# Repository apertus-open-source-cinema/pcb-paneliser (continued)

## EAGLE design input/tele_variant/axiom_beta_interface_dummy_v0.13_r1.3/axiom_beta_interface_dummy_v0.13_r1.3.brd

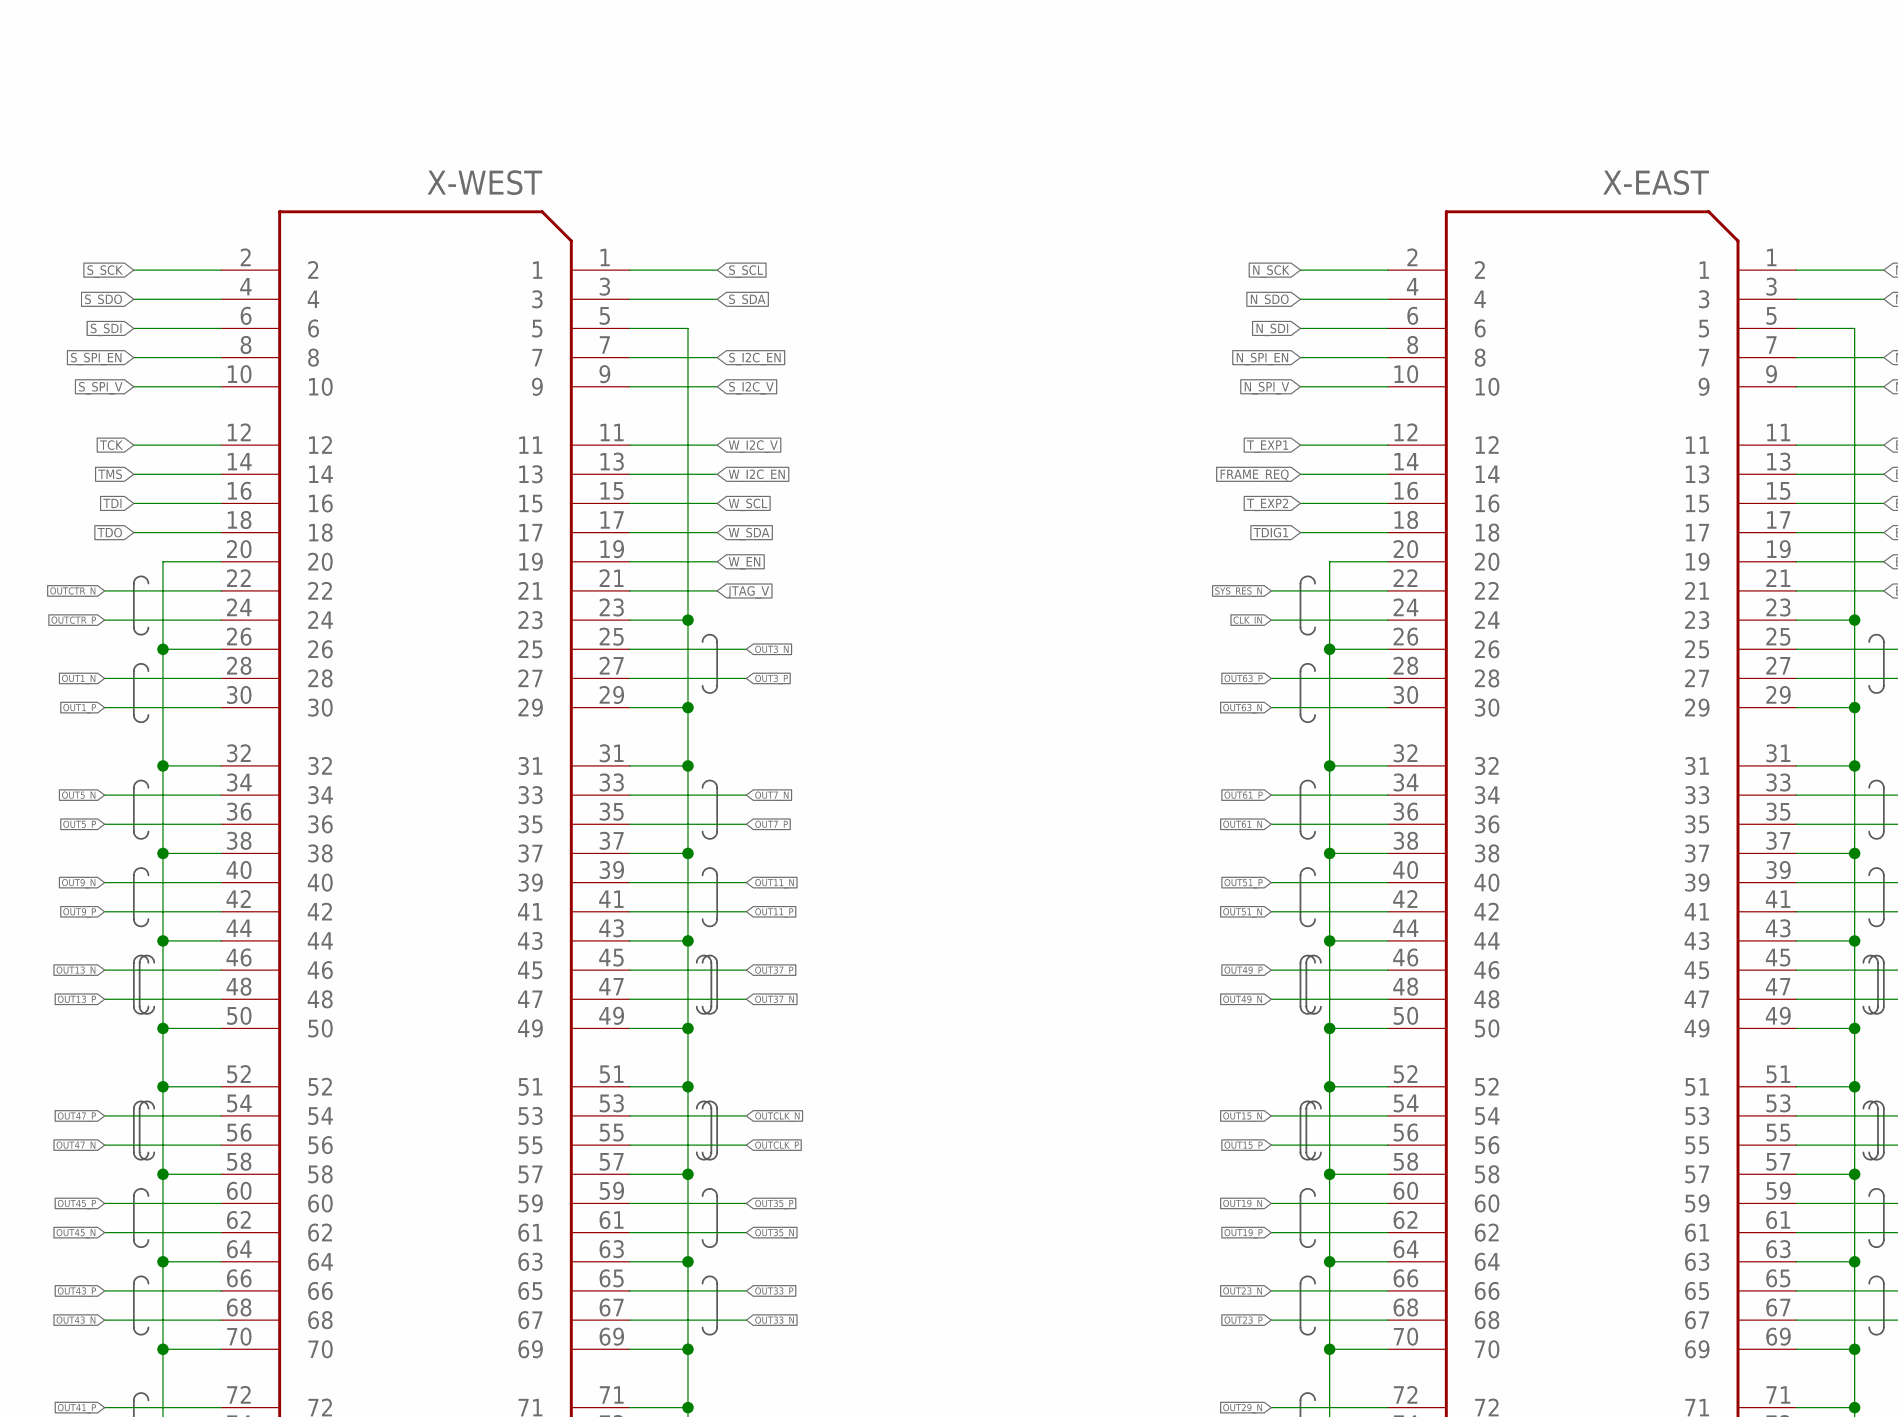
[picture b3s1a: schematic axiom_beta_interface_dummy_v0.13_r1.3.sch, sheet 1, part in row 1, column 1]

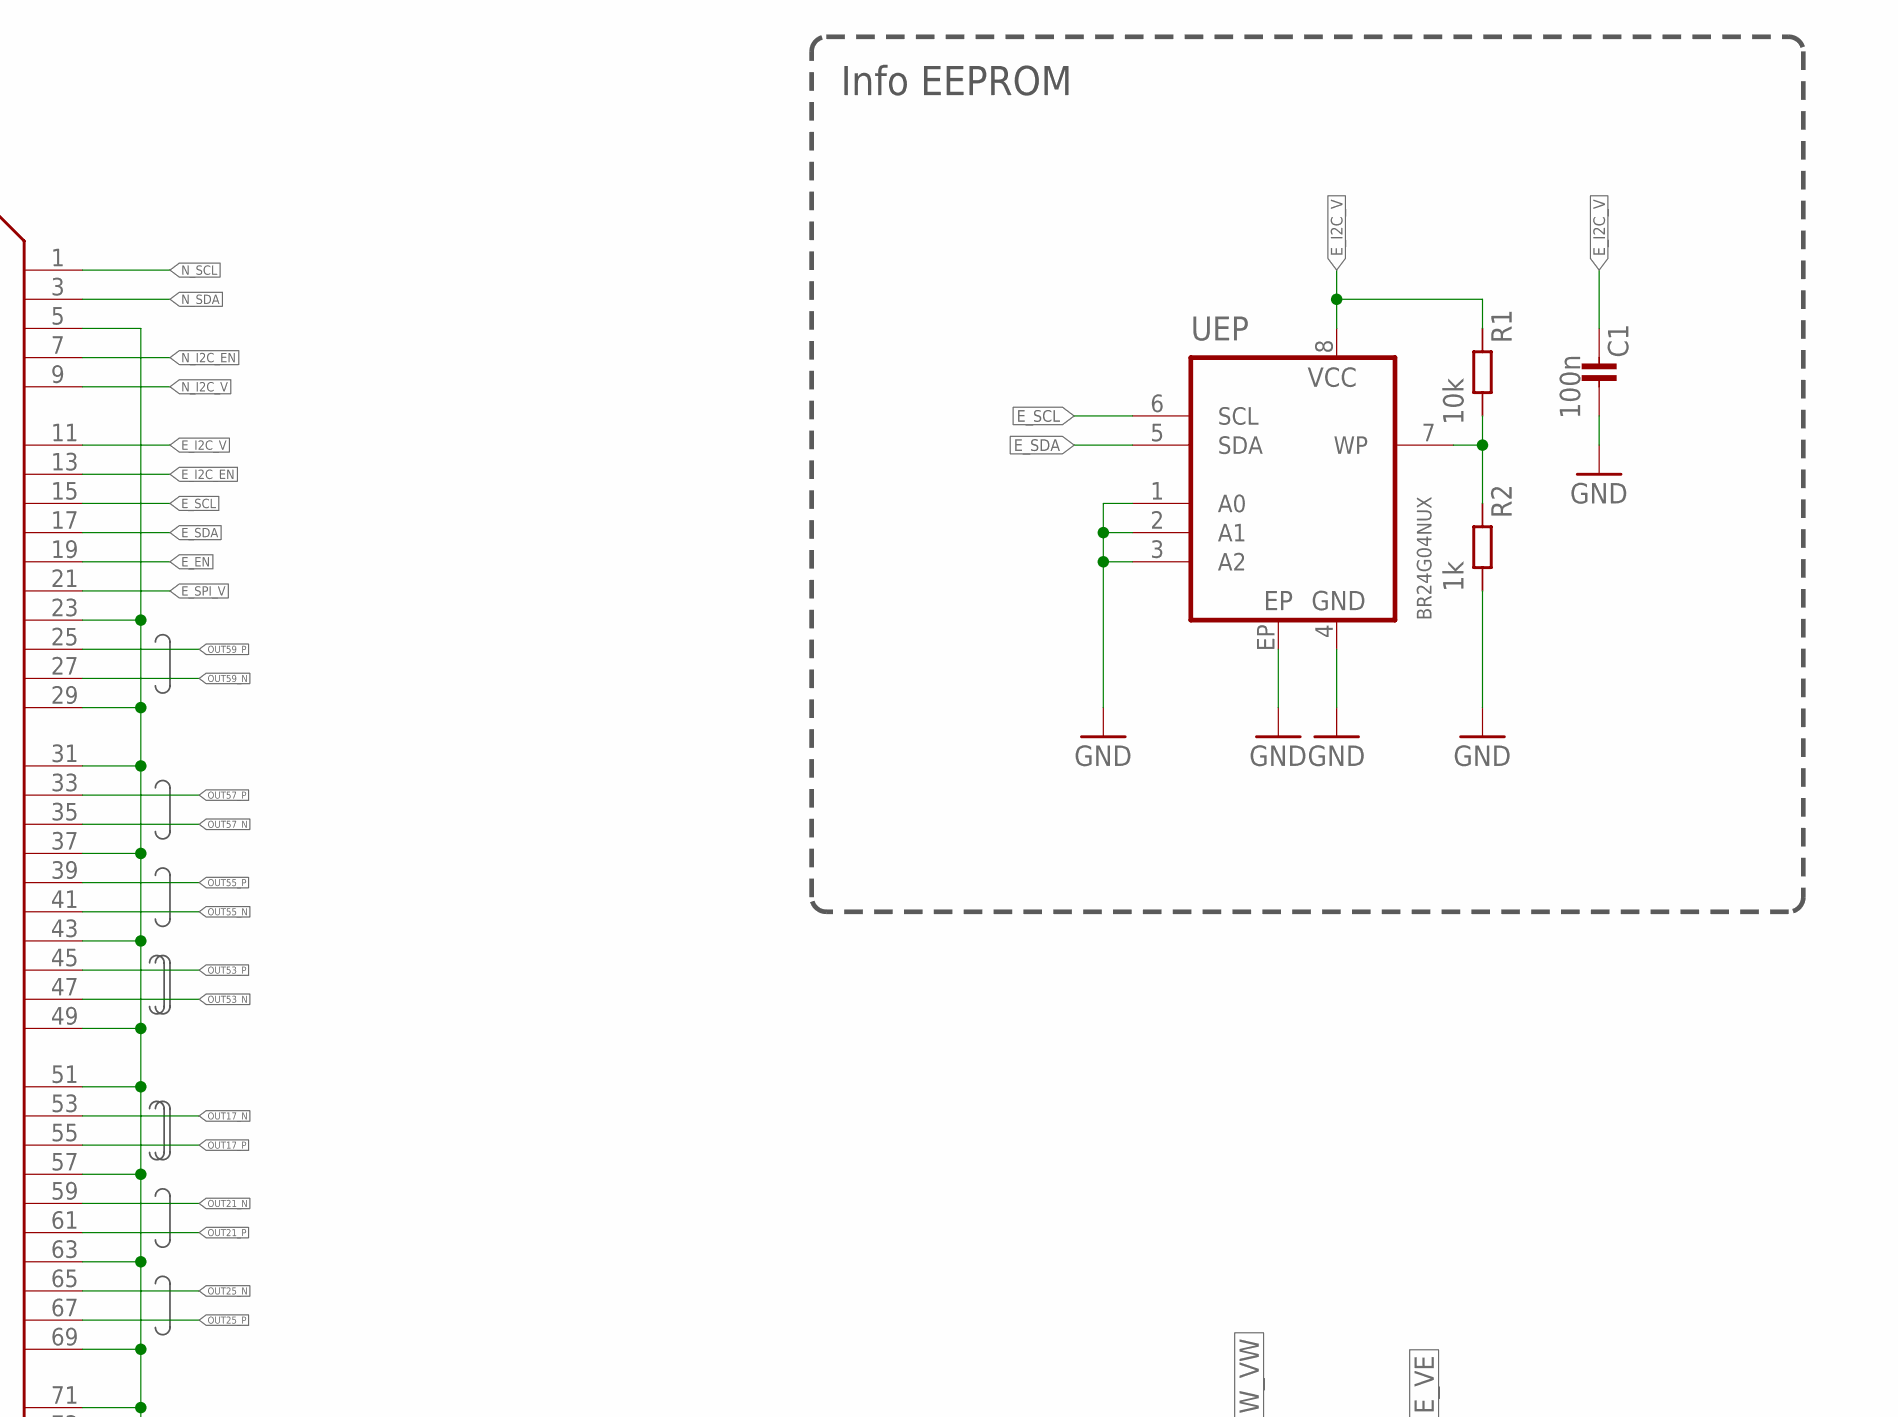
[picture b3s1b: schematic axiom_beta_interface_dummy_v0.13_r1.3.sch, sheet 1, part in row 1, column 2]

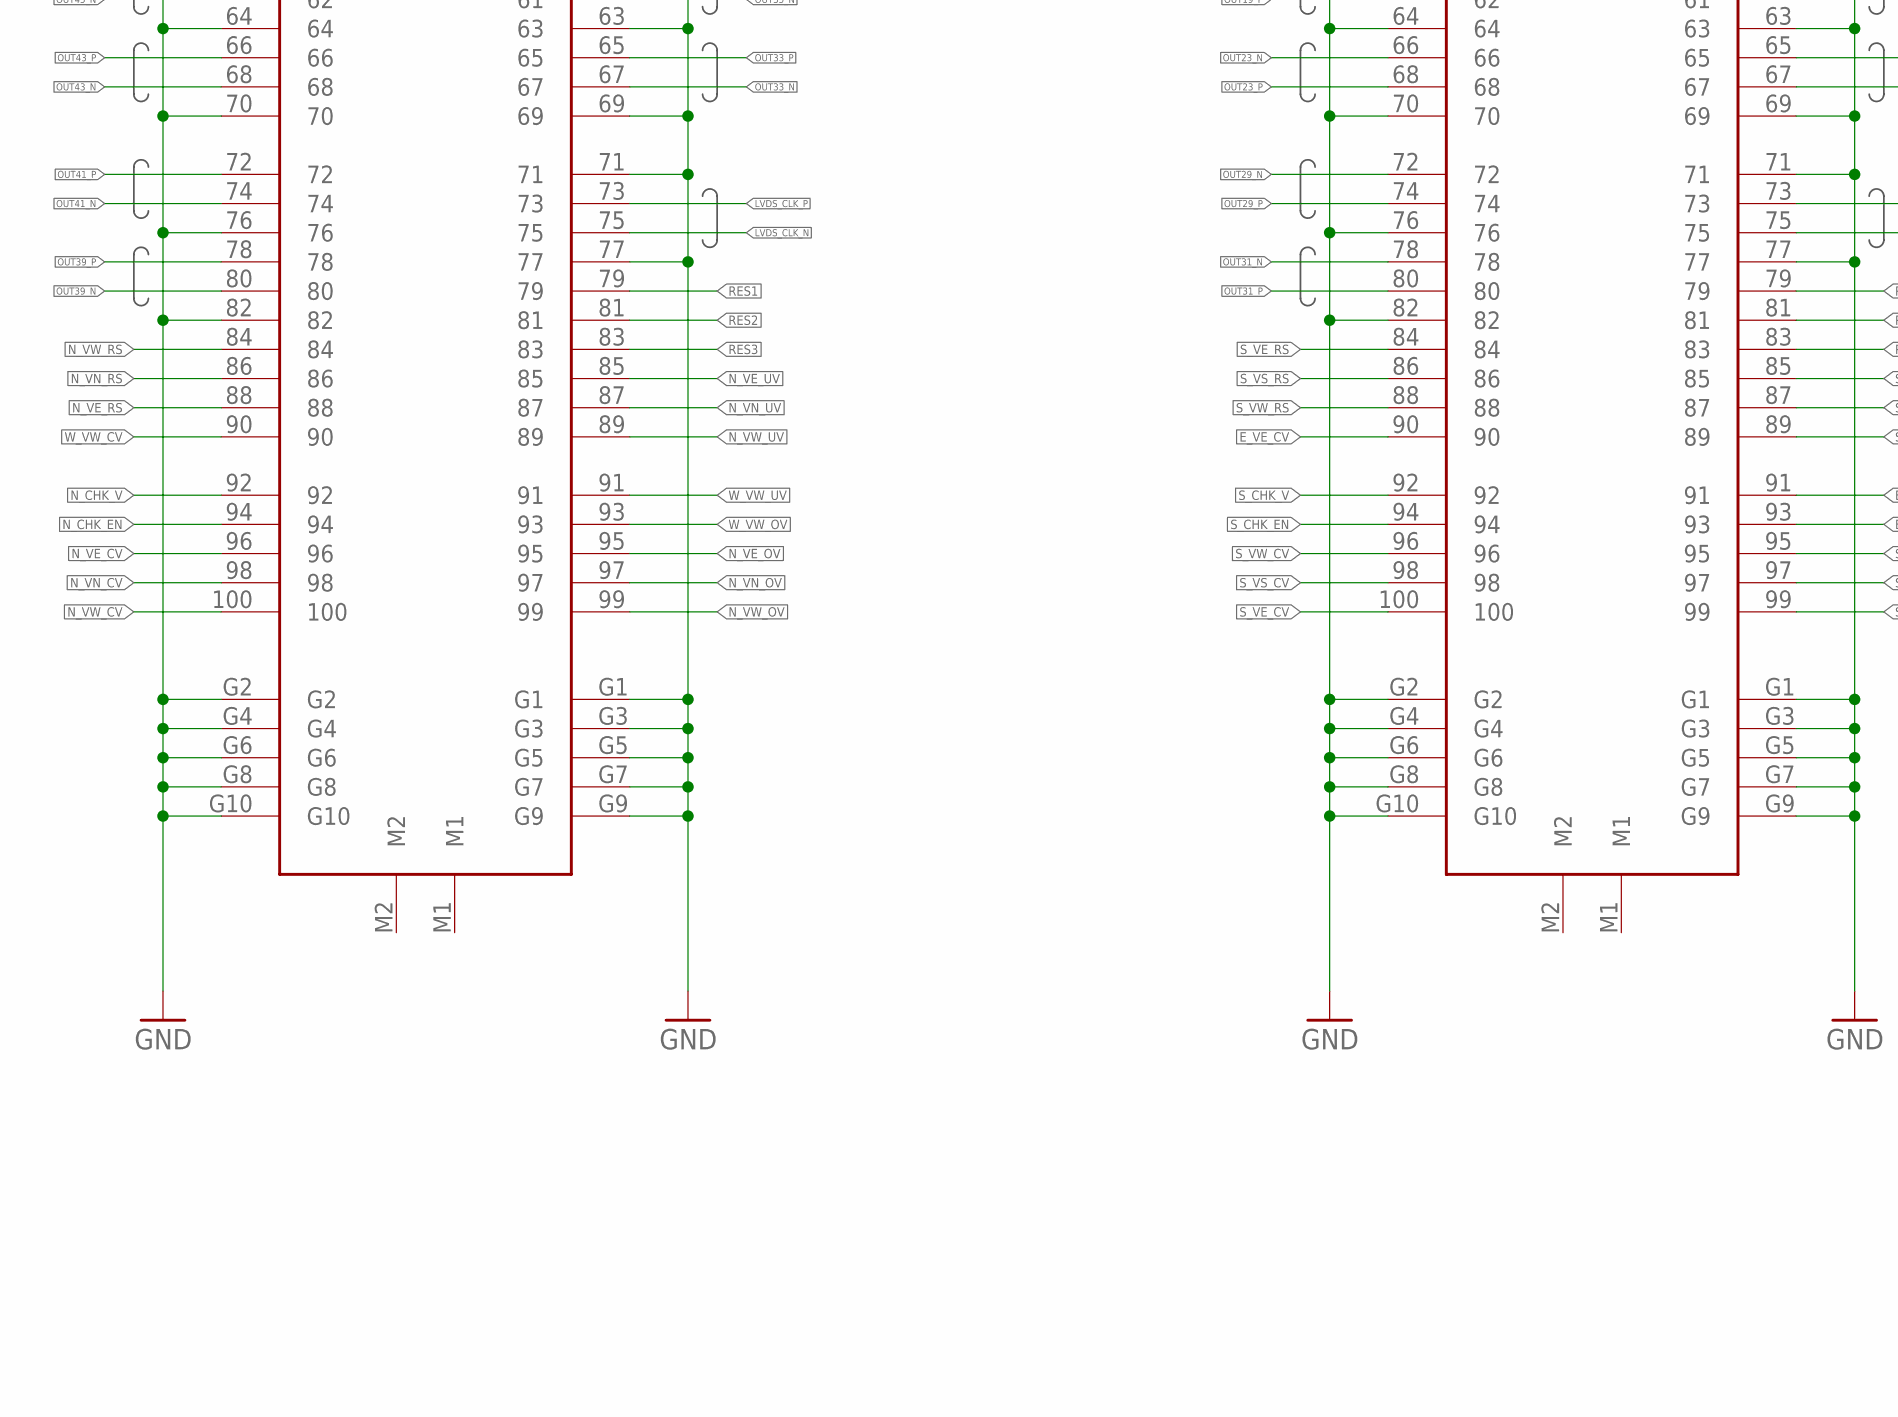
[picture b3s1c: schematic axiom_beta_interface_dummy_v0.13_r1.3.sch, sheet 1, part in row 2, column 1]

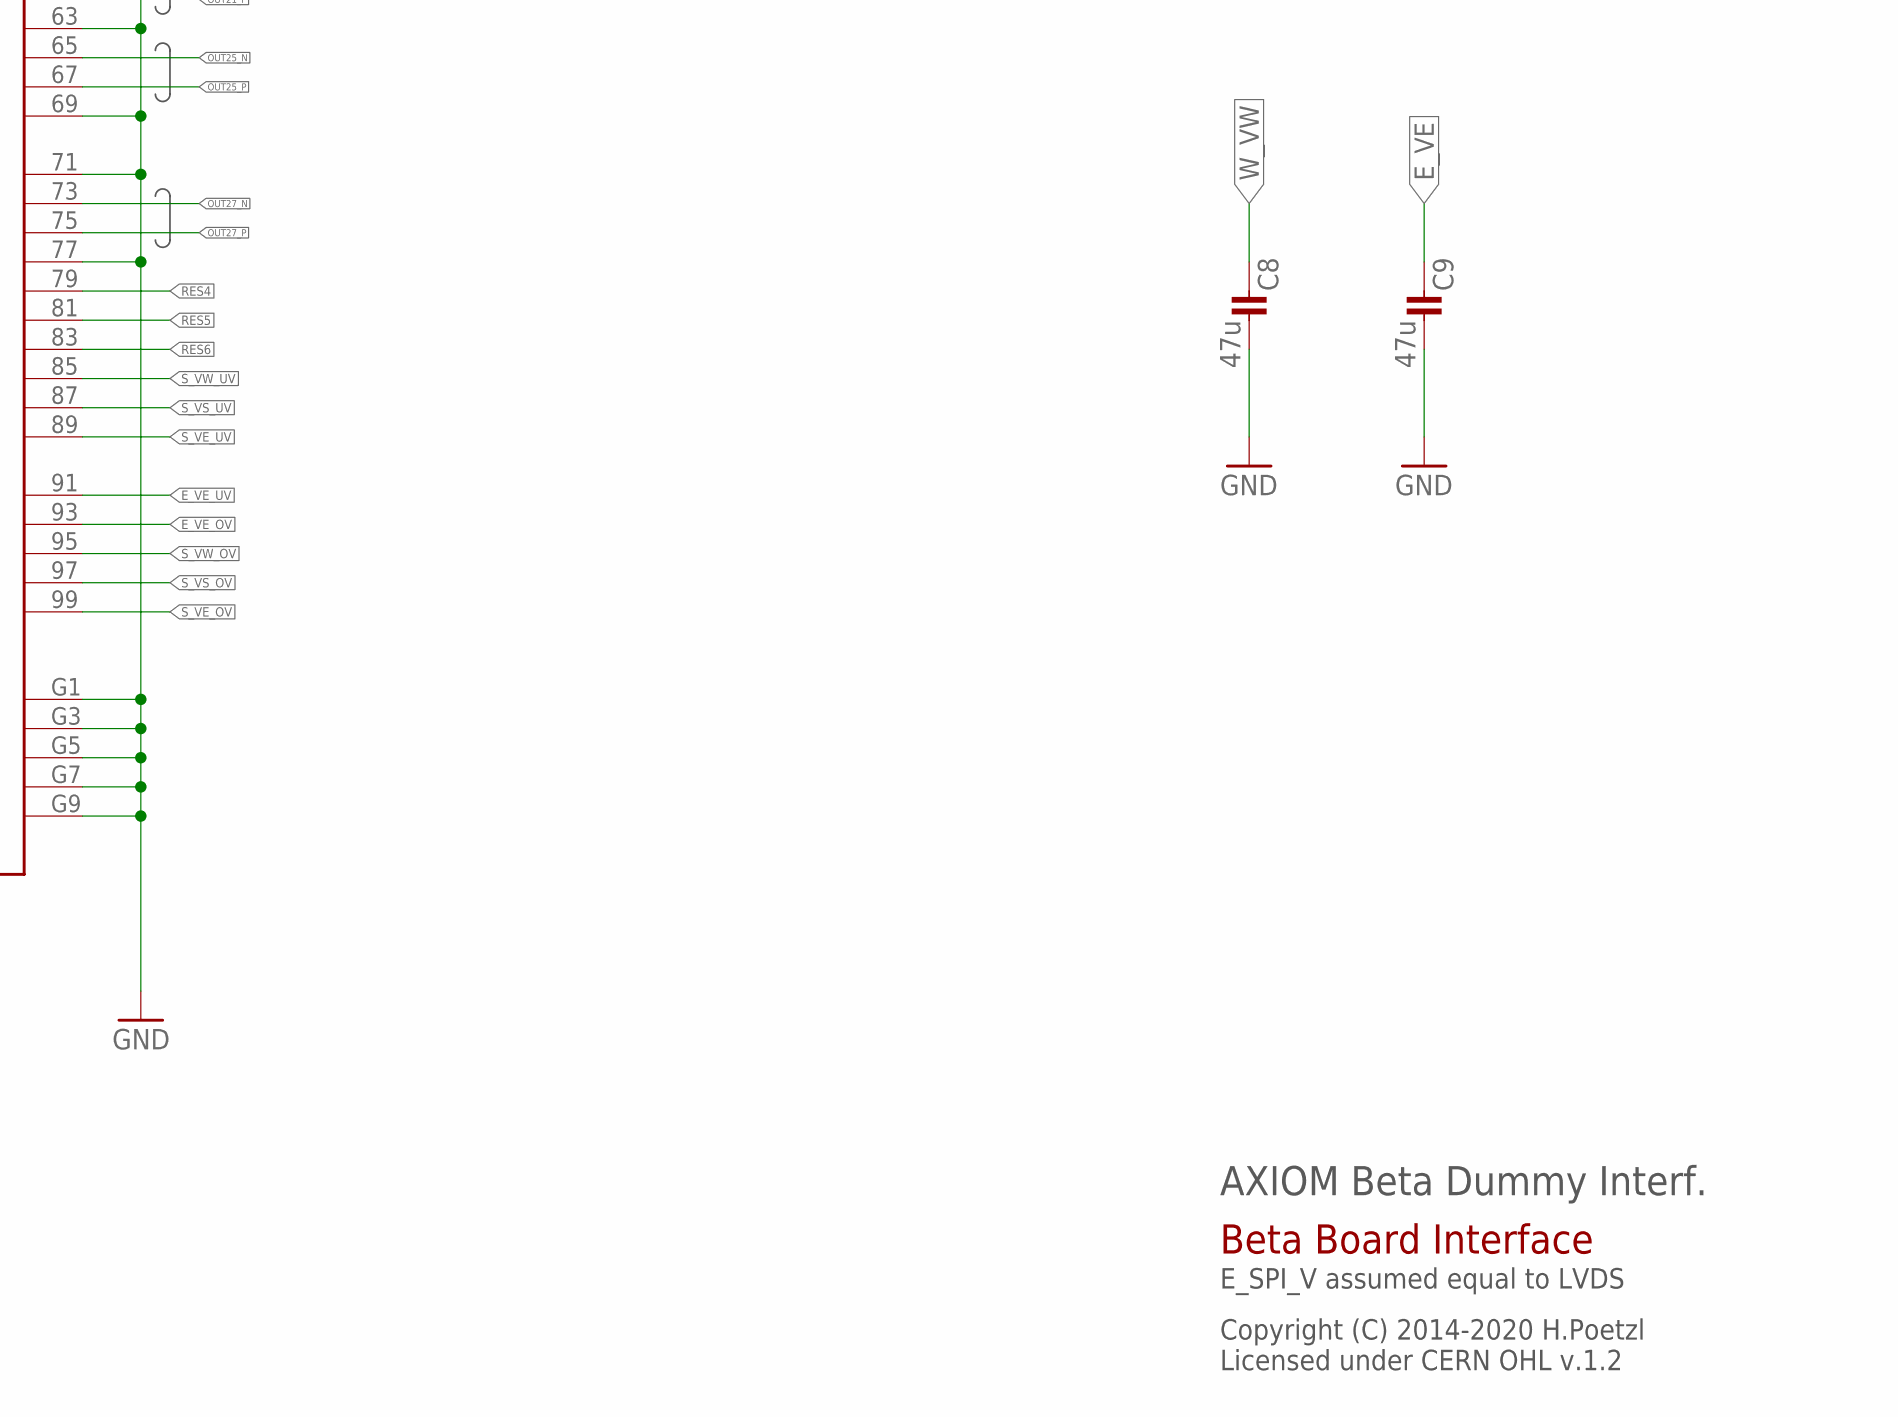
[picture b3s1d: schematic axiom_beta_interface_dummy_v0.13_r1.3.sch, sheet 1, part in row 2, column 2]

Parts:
C1: 100n; 0402-B
C8, C9: 47u; 0805-B
R1: 10k; 0402-B
R2: 1k; 0402-B
UEP: BR24G04NUX; DFN200X300X100-9N
X-EAST: FX10-100/10P; FX10A-100P/10
X-WEST: FX10-100/10P; FX10A-100P/10

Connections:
CLK_IN: X-EAST.24; also elsewhere on the board
E_EN: X-EAST.19
E_I2C_EN: X-EAST.13
E_I2C_V: C1.1, R1.1, UEP.8 (VCC), X-EAST.11
E_SCL: UEP.6 (SCL), X-EAST.15
E_SDA: UEP.5 (SDA), X-EAST.17
E_SPI_V: X-EAST.21
E_VE: C9.1; also elsewhere on the board
E_VE_CV: X-EAST.90
E_VE_OV: X-EAST.93
E_VE_UV: X-EAST.91
FRAME_REQ: X-EAST.14; also elsewhere on the board
GND: C1.2, C8.2, C9.2, R2.2, UEP.1 (A0), UEP.2 (A1), UEP.3 (A2), UEP.4 (GND), UEP.EP, X-EAST.5, X-EAST.20, X-EAST.23, X-EAST.26, X-EAST.29, X-EAST.31, X-EAST.32, X-EAST.37, X-EAST.38, X-EAST.43, X-EAST.44, X-EAST.49, X-EAST.50, X-EAST.51, X-EAST.52, X-EAST.57, X-EAST.58, X-EAST.63, X-EAST.64, X-EAST.69, X-EAST.70, X-EAST.71, X-EAST.76, X-EAST.77, X-EAST.82, X-EAST.G1, X-EAST.G2, X-EAST.G3, X-EAST.G4, X-EAST.G5, X-EAST.G6, X-EAST.G7, X-EAST.G8, X-EAST.G9, X-EAST.G10, X-WEST.5, X-WEST.20, X-WEST.23, X-WEST.26, X-WEST.29, X-WEST.31, X-WEST.32, X-WEST.37, X-WEST.38, X-WEST.43, X-WEST.44, X-WEST.49, X-WEST.50, X-WEST.51, X-WEST.52, X-WEST.57, X-WEST.58, X-WEST.63, X-WEST.64, X-WEST.69, X-WEST.70, X-WEST.71, X-WEST.76, X-WEST.77, X-WEST.82, X-WEST.G1, X-WEST.G2, X-WEST.G3, X-WEST.G4, X-WEST.G5, X-WEST.G6, X-WEST.G7, X-WEST.G8, X-WEST.G9, X-WEST.G10; also elsewhere on the board
JTAG_V: X-WEST.21
LVDS_CLK_N: X-WEST.75; also elsewhere on the board
LVDS_CLK_P: X-WEST.73; also elsewhere on the board
unnamed: R1.2, R2.1, UEP.7 (WP)
N_CHK_EN: X-WEST.94; also elsewhere on the board
N_CHK_V: X-WEST.92; also elsewhere on the board
N_I2C_EN: X-EAST.7; also elsewhere on the board
N_I2C_V: X-EAST.9; also elsewhere on the board
N_SCK: X-EAST.2; also elsewhere on the board
N_SCL: X-EAST.1; also elsewhere on the board
N_SDA: X-EAST.3; also elsewhere on the board
N_SDI: X-EAST.6; also elsewhere on the board
N_SDO: X-EAST.4; also elsewhere on the board
N_SPI_EN: X-EAST.8; also elsewhere on the board
N_SPI_V: X-EAST.10; also elsewhere on the board
N_VE_CV: X-WEST.96; also elsewhere on the board
N_VE_OV: X-WEST.95; also elsewhere on the board
N_VE_RS: X-WEST.88; also elsewhere on the board
N_VE_UV: X-WEST.85; also elsewhere on the board
N_VN_CV: X-WEST.98; also elsewhere on the board
N_VN_OV: X-WEST.97; also elsewhere on the board
N_VN_RS: X-WEST.86; also elsewhere on the board
N_VN_UV: X-WEST.87; also elsewhere on the board
N_VW_CV: X-WEST.100; also elsewhere on the board
N_VW_OV: X-WEST.99; also elsewhere on the board
N_VW_RS: X-WEST.84; also elsewhere on the board
N_VW_UV: X-WEST.89; also elsewhere on the board
OUT1_N: X-WEST.28; also elsewhere on the board
OUT1_P: X-WEST.30; also elsewhere on the board
OUT3_N: X-WEST.25; also elsewhere on the board
OUT3_P: X-WEST.27; also elsewhere on the board
OUT5_N: X-WEST.34; also elsewhere on the board
OUT5_P: X-WEST.36; also elsewhere on the board
OUT7_N: X-WEST.33; also elsewhere on the board
OUT7_P: X-WEST.35; also elsewhere on the board
OUT9_N: X-WEST.40; also elsewhere on the board
OUT9_P: X-WEST.42; also elsewhere on the board
OUT11_N: X-WEST.39; also elsewhere on the board
OUT11_P: X-WEST.41; also elsewhere on the board
OUT13_N: X-WEST.46; also elsewhere on the board
OUT13_P: X-WEST.48; also elsewhere on the board
OUT15_N: X-EAST.54; also elsewhere on the board
OUT15_P: X-EAST.56; also elsewhere on the board
OUT17_N: X-EAST.53; also elsewhere on the board
OUT17_P: X-EAST.55; also elsewhere on the board
OUT19_N: X-EAST.60; also elsewhere on the board
OUT19_P: X-EAST.62; also elsewhere on the board
OUT21_N: X-EAST.59; also elsewhere on the board
OUT21_P: X-EAST.61; also elsewhere on the board
OUT23_N: X-EAST.66; also elsewhere on the board
OUT23_P: X-EAST.68; also elsewhere on the board
OUT25_N: X-EAST.65; also elsewhere on the board
OUT25_P: X-EAST.67; also elsewhere on the board
OUT27_N: X-EAST.73; also elsewhere on the board
OUT27_P: X-EAST.75; also elsewhere on the board
OUT29_N: X-EAST.72; also elsewhere on the board
OUT29_P: X-EAST.74; also elsewhere on the board
OUT31_N: X-EAST.78; also elsewhere on the board
OUT31_P: X-EAST.80; also elsewhere on the board
OUT33_N: X-WEST.67; also elsewhere on the board
OUT33_P: X-WEST.65; also elsewhere on the board
OUT35_N: X-WEST.61; also elsewhere on the board
OUT35_P: X-WEST.59; also elsewhere on the board
OUT37_N: X-WEST.47; also elsewhere on the board
OUT37_P: X-WEST.45; also elsewhere on the board
OUT39_N: X-WEST.80; also elsewhere on the board
OUT39_P: X-WEST.78; also elsewhere on the board
OUT41_N: X-WEST.74; also elsewhere on the board
OUT41_P: X-WEST.72; also elsewhere on the board
OUT43_N: X-WEST.68; also elsewhere on the board
OUT43_P: X-WEST.66; also elsewhere on the board
OUT45_N: X-WEST.62; also elsewhere on the board
OUT45_P: X-WEST.60; also elsewhere on the board
OUT47_N: X-WEST.56; also elsewhere on the board
OUT47_P: X-WEST.54; also elsewhere on the board
OUT49_N: X-EAST.48; also elsewhere on the board
OUT49_P: X-EAST.46; also elsewhere on the board
OUT51_N: X-EAST.42; also elsewhere on the board
OUT51_P: X-EAST.40; also elsewhere on the board
OUT53_N: X-EAST.47; also elsewhere on the board
OUT53_P: X-EAST.45; also elsewhere on the board
OUT55_N: X-EAST.41; also elsewhere on the board
OUT55_P: X-EAST.39; also elsewhere on the board
OUT57_N: X-EAST.35; also elsewhere on the board
OUT57_P: X-EAST.33; also elsewhere on the board
OUT59_N: X-EAST.27; also elsewhere on the board
OUT59_P: X-EAST.25; also elsewhere on the board
OUT61_N: X-EAST.36; also elsewhere on the board
OUT61_P: X-EAST.34; also elsewhere on the board
OUT63_N: X-EAST.30; also elsewhere on the board
OUT63_P: X-EAST.28; also elsewhere on the board
OUTCLK_N: X-WEST.53; also elsewhere on the board
OUTCLK_P: X-WEST.55; also elsewhere on the board
OUTCTR_N: X-WEST.22; also elsewhere on the board
OUTCTR_P: X-WEST.24; also elsewhere on the board
RES1: X-WEST.79
RES2: X-WEST.81
RES3: X-WEST.83
RES4: X-EAST.79
RES5: X-EAST.81
RES6: X-EAST.83
SYS_RES_N: X-EAST.22; also elsewhere on the board
S_CHK_EN: X-EAST.94; also elsewhere on the board
S_CHK_V: X-EAST.92; also elsewhere on the board
S_I2C_EN: X-WEST.7; also elsewhere on the board
S_I2C_V: X-WEST.9; also elsewhere on the board
S_SCK: X-WEST.2; also elsewhere on the board
S_SCL: X-WEST.1; also elsewhere on the board
S_SDA: X-WEST.3; also elsewhere on the board
S_SDI: X-WEST.6; also elsewhere on the board
S_SDO: X-WEST.4; also elsewhere on the board
S_SPI_EN: X-WEST.8; also elsewhere on the board
S_SPI_V: X-WEST.10; also elsewhere on the board
S_VE_CV: X-EAST.100; also elsewhere on the board
S_VE_OV: X-EAST.99; also elsewhere on the board
S_VE_RS: X-EAST.84; also elsewhere on the board
S_VE_UV: X-EAST.89; also elsewhere on the board
S_VS_CV: X-EAST.98; also elsewhere on the board
S_VS_OV: X-EAST.97; also elsewhere on the board
S_VS_RS: X-EAST.86; also elsewhere on the board
S_VS_UV: X-EAST.87; also elsewhere on the board
S_VW_CV: X-EAST.96; also elsewhere on the board
S_VW_OV: X-EAST.95; also elsewhere on the board
S_VW_RS: X-EAST.88; also elsewhere on the board
S_VW_UV: X-EAST.85; also elsewhere on the board
TCK: X-WEST.12
TDI: X-WEST.16
TDIG1: X-EAST.18; also elsewhere on the board
TDO: X-WEST.18
TMS: X-WEST.14
T_EXP1: X-EAST.12; also elsewhere on the board
T_EXP2: X-EAST.16; also elsewhere on the board
W_EN: X-WEST.19
W_I2C_EN: X-WEST.13
W_I2C_V: X-WEST.11
W_SCL: X-WEST.15
W_SDA: X-WEST.17
W_VW: C8.1; also elsewhere on the board
W_VW_CV: X-WEST.90
W_VW_OV: X-WEST.93
W_VW_UV: X-WEST.91

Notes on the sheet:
Info EEPROM
AXIOM Beta Dummy Interf.
Copyright (C) 2014-2020 H.Poetzl Licensed under CERN OHL v.1.2
Beta Board Interface
E_SPI_V assumed equal to LVDS

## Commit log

2020-07-02 - Added first implementation
2020-07-02 - Cleanup
2020-07-02 added a few elements
2020-07-02 removed PB - obsolete
2020-07-02 - Added fiducials and more layers
2020-07-02 naming unified and origin elements added
2020-07-03 updated for python 3
2020-07-05 Update generate_mixed_beta_panel.py
    all fiducials added
    origin added
    subpanel label added
    added silkscreen layer
    fixed output file name for soldermask layer
2020-07-05 update
    added a bunch of additiona layers
    switched to eagle layer naming scheme
2020-07-05 update
    added drill merging
    (still some bug left that scales drills wrong)
2020-07-05 - Adjusted drill settings for proper export
2020-07-13 stage 2
    renamed output paths
    renamed scripts
    fixed typo in generation script
    stage2 script started but output is not as intended yet
2020-07-13 clean up
2020-07-15 - Fixed export for large boards
2020-07-16 gitingore update to ingore outputs
2020-07-16 3x4 grid subpanels
2020-07-16 label placement update
2020-07-21 - Added removal of board outlines from Gerber files
2020-07-21 - Added new PCBs with adjusted outline and output of elapsed time
2020-07-26 - Added missing Gerber files
2020-07-26 - Added missing Excellon files
2020-07-26 fixed naming in stage2 script
2020-07-26 added output
2020-07-26 - Removed outline of stage 1, added output result files
2020-07-27 - Added subpanel bridges
2020-07-27 - Added mouse bites
2020-08-03 updated output
2020-10-04 - Added rotated gerber files (through gerbv) and related shell script
2020-10-04 - Pushed adjusted stage1 script and output
2020-10-04 - Adjusted stage2, added new output, drill layer has problems, probably import from stage1 has wrong format
2020-10-04 added note
2020-10-04 - Fixed drill layer export
2020-10-04 - Adjusted notes
2020-11-07 added cam job with modified layer names
2020-11-07 updated cam usage
2020-11-07 - Updated gerber data and exported panels
2020-11-07 - Exported stage 1 with outline
2020-11-07 - Added stencil script for stage 1, also added result file
2020-11-08 removed layer 121
2020-11-08 updated export guide
2020-11-08 - Exported new data
2020-11-08 - Added temporary folder to place support data and keep output clean
2020-11-11 Rename eagle-export-guide.md to README.md
2020-11-11 - Updated boards to new revisions, adjusted rotation script
2020-11-11 - Removed old folders and files
2020-11-11 - Removed old archives
2020-11-14 - Added new PCB version and stage 1 output
2020-11-15 added tele and base variant inputs
2020-11-15 - Updated PB and MB board rotation, adjusted paths
2020-11-15 - Rotated PB and MB in Tele variant
2020-11-15 - Added EAGLE files
2020-11-15 - Added component position data
2020-11-16 - Added first version of PNP data extractor
2020-11-16 - Committed correct .asc file
2020-11-16 - Added rotation limit
2020-11-17 fixed creating temp dir
2020-11-17 fixed not running setup()
2020-11-17 base -> tele assembly variant
2020-11-17 updated after mb base -> tele fix
2020-11-17 - Added rounding of floats to limit decimals to 3
2020-11-18 - Added loading of Tele IDs from BOM
2020-11-18 updated subpanel label
2020-11-18 "µZ" symbol removed
2020-11-18 updated powerboard gerber
2020-11-18 rotation instructions added
2020-11-18 updated coordinates and subpanel label
2020-11-18 - Updated stage 1 output
2020-11-18 moved subpanel-label to other side
2020-11-18 cutout size 2.5 -> 2.54mm
2020-11-18 added teststrip
2020-11-18 removed gpi files
2020-11-18 added test strip to stage 1
2020-11-18 added empty
2020-11-18 moved teststrip folder
2020-11-18 - Adjusted strip location
2020-11-18 - Added correct output
2020-11-18 - Added additional parameters to merge outline correctly
2020-11-18 - Added fixed strip
2020-11-18 - Exported strip with XLN 33MM
2020-11-19 removed *.gpi
2020-11-19 added *.gpi to gitignore
2020-11-19 added teststrip V0.1 R1.1
2020-11-19 fixed drill scaling output
2020-11-19 - Fixed drill layer loading, format is set to 2.4
2020-11-19 updated all boards and gerbers
2020-11-19 reverting to none modified drills for test strip
2020-11-19 - Uploaded updated input and output data
2020-11-20 added script to convert naming scheme for jlcpcb
2020-11-20 added jlc id source and gerber
2020-11-20 - Added JLCPCB silkscreen
2020-11-20 - Added label for JLCPCB
2020-11-21 fixed error
2020-11-22 file names more like https://support.jlcpcb.com/article/29-suggested-naming-patterns now
2020-11-27 - Added adjusted output for JLCPCB
2020-11-27 - Updated JLCPCB output with correct variant
2020-11-27 - Added stage 1 generator script for JLCPCB variant
2020-11-27 - Added JLCPCB variant gerber files
2020-11-27 moved jlcpcb specific input files into base folder
2020-11-27 added jlcpcb renamed output and converter script
2020-11-27 removed jlc label merging from normal output
2020-11-28 - Added BOM processor, which fills up infos in the BOM
2020-11-28 Removed old BOM
2020-11-28 - Adjusted BOM processor to determine the component side correctly
2020-12-07 added reference boards (eagle and gerber)
2020-12-07 rotated input base variants and added new reference panel script and output
2020-12-07 added script to convert gerber to pngs plus the resulting pngs
2020-12-08 added new SB version that contains netclass properties about LVDS traces
2020-12-08 added impedance extraction script and preliminary results
2020-12-08 added bottom copper layer extraction
2020-12-08 new approach for impedance trace extraction
2020-12-08 added latest eagle file versions
2020-12-08 commited updated gerbers
2020-12-08 updated stage1 panel and rotated inputs gerbers
2020-12-08 updated impedance extraction script and results
2020-12-08 impedance extracted exported gerbers added for panelization
2020-12-08 impedance stage1 panelization updated and output added
2020-12-08 removed faulty boardoutline, not needed
2020-12-09 MB & PB V0.38 added
2020-12-09 updated subpanel label version/date
2020-12-09 new rotated mb/pb and new panel output
2020-12-09 added latest board sources
2020-12-09 added latest gerber outputs
2020-12-09 rotated gerbers and updated versions in panelizer script
2020-12-09 stage1 panel output updated
2020-12-09 - Added dynamic text for labels through HersheyFonts
2020-12-09 updated requirements with Hershey-Fonts
2020-12-09 updated mixed subpanel label generation and output
2020-12-09 subpanel label thickness increased to 0.2
2020-12-10 new IB added
2020-12-10 new panel V0.42 pushed
2020-12-18 new versions of boards added
2020-12-18 added new version gerber output and stage1 script adaptions
2020-12-18 rotated mainboard and powerboard and new stage 1 output
2020-12-18 updated impedance extraction board files
2020-12-18 new gerber outputs of imepdance isolated added
2020-12-18 impedance isolated output added, rotated originals removed
2020-12-22 updated impedance settings in teststrip and powerboard
2020-12-22 updated impedance filtered output brds
2020-12-22 updated impedance filtered gerber output
2020-12-22 updated impedance output gerber
2020-12-22 updated MB
2020-12-22 new impedance filtering update
2020-12-22 updated MB gerber output
2020-12-22 updated outsputs of impedance gerbers
2020-12-22 updated impedance filtered output
2020-12-22 impedance output fixed
2021-01-07 added top/bottom cream layers in tele variant for stencil creation
2021-01-07 new script to generate stencil of stage1 mixed panel
2021-01-07 reworked stencil input gerbers
2021-01-07 added rotation scripts
2021-01-07 stencil generation script plus notes in it
2021-01-07 rotation script added
2021-01-07 input stencil files updated
2021-01-07 stencil output added/updated
2021-01-07 updated rotated output
2021-01-10 updated pb with b2b connectors enabled in tele variant
2021-01-10 updated mb stencil inputs
2021-01-10 stencil output updated
2021-01-28 added new pb version
2021-01-28 pb outputs updated
2021-01-28 updated new PB
2021-01-28 stencil updated
2021-01-31 - Updated PCBs and output of stage 1
2021-02-01 - Reworked drawing order, now exported data is used to ensure correct placement - Added text drawing - Several small adjustments
2021-02-01 - Fixed offset problem, by inserting right cutout width of 2.54 and not 2.5 like before - Cleanup required
2021-02-01 - Added marker for first pin to be able to verify rotation for production
2021-02-02 updated stencil with fiducial engrave marks
2021-02-02 - Fixed problems with "first pin"
2021-02-02 - Fixed BOM handling
2021-02-02 - Fixed BOM file path
2021-02-02 fixed input file name
2021-02-02 - Small cleanup and adjustments
2021-02-02 added soldermask and copper layers to stencil generation
2021-02-02 pnp output added
2021-02-02 tele variant copper and soldermask gerber layers added & cleanup of old versions
2021-02-02 reference stage removed
2021-02-02 stencil output copper and soldermask results
2021-02-02 stencil copper / soldermask output updated
2021-02-02 unrotated removed
2021-02-02 stencil copper/soldermask fixed
2021-02-02 stencil clean up
2021-02-03 removed jlcpcb related stuff
2021-02-03 eagle folder clean up
2021-02-03 JX1 added to PB pnp
2021-02-03 updated pnp output
2021-02-03 updated JX1/JX2 in MB mnb
2021-02-03 stencil and pnp creation update
2021-02-05 - Reworked PNP generation script
2022-10-16 added hdmi plugin module
2022-10-17 Refactoring, added script for HDMI module sub-panel
2022-10-17 pushed hdmi plugin module component placements
